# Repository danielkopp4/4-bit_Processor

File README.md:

# 4-bit_Processor
This is a project to build a fully working 4-bit processor made with discrete logic gates.
The processor is programmed with an Arduino MEGA and can be programmed in the assembly language based off of my architecture.

The schematics can currently be found in the Schematics branch. The file type of the schematics is for KiCAD.
The RAM and ROM have an associated PCB design.

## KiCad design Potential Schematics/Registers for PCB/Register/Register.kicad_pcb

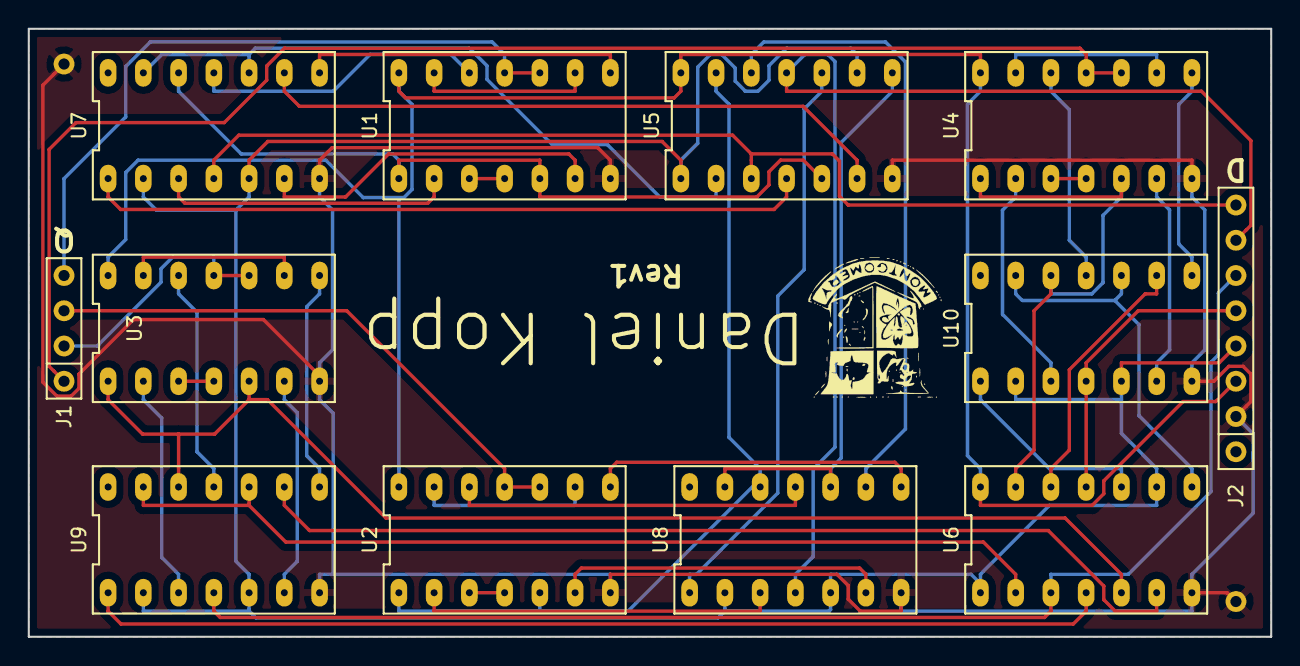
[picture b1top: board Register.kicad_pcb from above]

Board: 2 copper layers, 89.5 x 43.8 mm, 15 parts (0 on the bottom side), 51 nets.

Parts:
 : Measurement_Point_Round-TH_Small
 #2: Measurement_Point_Round-TH_Small
 #3: Real_Logo
J1: Conn_01x04_Female; Female_Header_4-pin
J2: Conn_01x08_Female; Female_Header_8-pin
U1, U2, U3, U4: 74LS02; DIP-14_300_ELL
U5, U6: 74LS04; DIP-14_300_ELL
U7, U8, U9, U10: 74LS08; DIP-14_300_ELL

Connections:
/D_Flip-Flop/D_Latch/QN: U1.3, U1.4
/D_Flip-Flop/D_Latch/RS-Latch/R: U1.2, U7.3
/D_Flip-Flop/D_Latch/RS-Latch/S: U1.6, U7.6
/D_Flip-Flop/QN: U1.9, U1.13
/D_Flip-Flop/sheet5BAD013C/C: U5.2, U7.10, U7.13
/D_Flip-Flop/sheet5BAD013C/D: U1.1, U1.5, U5.5, U7.12
/D_Flip-Flop/sheet5BAD013C/RS-Latch/R: U1.8, U7.8
/D_Flip-Flop/sheet5BAD013C/RS-Latch/S: U1.12, U7.11
/sheet5BAD03B0/D_Latch/QN: U2.3, U2.4
/sheet5BAD03B0/D_Latch/RS-Latch/R: U2.2, U8.3
/sheet5BAD03B0/D_Latch/RS-Latch/S: U2.6, U8.6
/sheet5BAD03B0/QN: U2.9, U2.13
/sheet5BAD03B0/sheet5BAD013C/C: U5.8, U8.10, U8.13
/sheet5BAD03B0/sheet5BAD013C/D: U2.1, U2.5, U5.13, U8.12
/sheet5BAD03B0/sheet5BAD013C/RS-Latch/R: U2.8, U8.8
/sheet5BAD03B0/sheet5BAD013C/RS-Latch/S: U2.12, U8.11
/sheet5BAD03B9/D_Latch/QN: U3.3, U3.4
/sheet5BAD03B9/D_Latch/RS-Latch/R: U3.2, U9.3
/sheet5BAD03B9/D_Latch/RS-Latch/S: U3.6, U9.6
/sheet5BAD03B9/QN: U3.9, U3.13
/sheet5BAD03B9/sheet5BAD013C/C: U6.2, U9.10, U9.13
/sheet5BAD03B9/sheet5BAD013C/D: U3.1, U3.5, U6.5, U9.12
/sheet5BAD03B9/sheet5BAD013C/RS-Latch/R: U3.8, U9.8
/sheet5BAD03B9/sheet5BAD013C/RS-Latch/S: U3.12, U9.11
/sheet5BAD03C0/D_Latch/QN: U4.3, U4.4
/sheet5BAD03C0/D_Latch/RS-Latch/R: U4.2, U10.3
/sheet5BAD03C0/D_Latch/RS-Latch/S: U4.6, U10.6
/sheet5BAD03C0/QN: U4.9, U4.13
/sheet5BAD03C0/sheet5BAD013C/C: U6.8, U10.10, U10.13
/sheet5BAD03C0/sheet5BAD013C/D: U4.1, U4.5, U6.13, U10.12
/sheet5BAD03C0/sheet5BAD013C/RS-Latch/R: U4.8, U10.8
/sheet5BAD03C0/sheet5BAD013C/RS-Latch/S: U4.12, U10.11
Clock: J2.4, U5.1, U5.9, U6.1, U6.9, U7.2, U7.5, U8.2, U8.5, U9.2, U9.5, U10.2, U10.5
D0: J2.8, U5.3, U7.4
D1: J2.7, U5.11, U8.4
D2: J2.6, U6.3, U9.4
D3: J2.5, U6.11, U10.4
GND: .1, #2.1, J2.2, U1.7, U2.7, U3.7, U4.7, U5.7, U6.7, U7.7, U8.7, U9.7, U10.7
unnamed: U5.4, U7.1
unnamed: U5.6, U7.9
unnamed: U5.10, U8.1
unnamed: U5.12, U8.9
unnamed: U6.4, U9.1
unnamed: U6.6, U9.9
unnamed: U6.10, U10.1
unnamed: U6.12, U10.9
Q0: J1.4, U1.10, U1.11
Q1: J1.3, U2.10, U2.11
Q2: J1.2, U3.10, U3.11
Q3: J1.1, U4.10, U4.11
VCC: J2.3, U1.14, U2.14, U3.14, U4.14, U5.14, U6.14

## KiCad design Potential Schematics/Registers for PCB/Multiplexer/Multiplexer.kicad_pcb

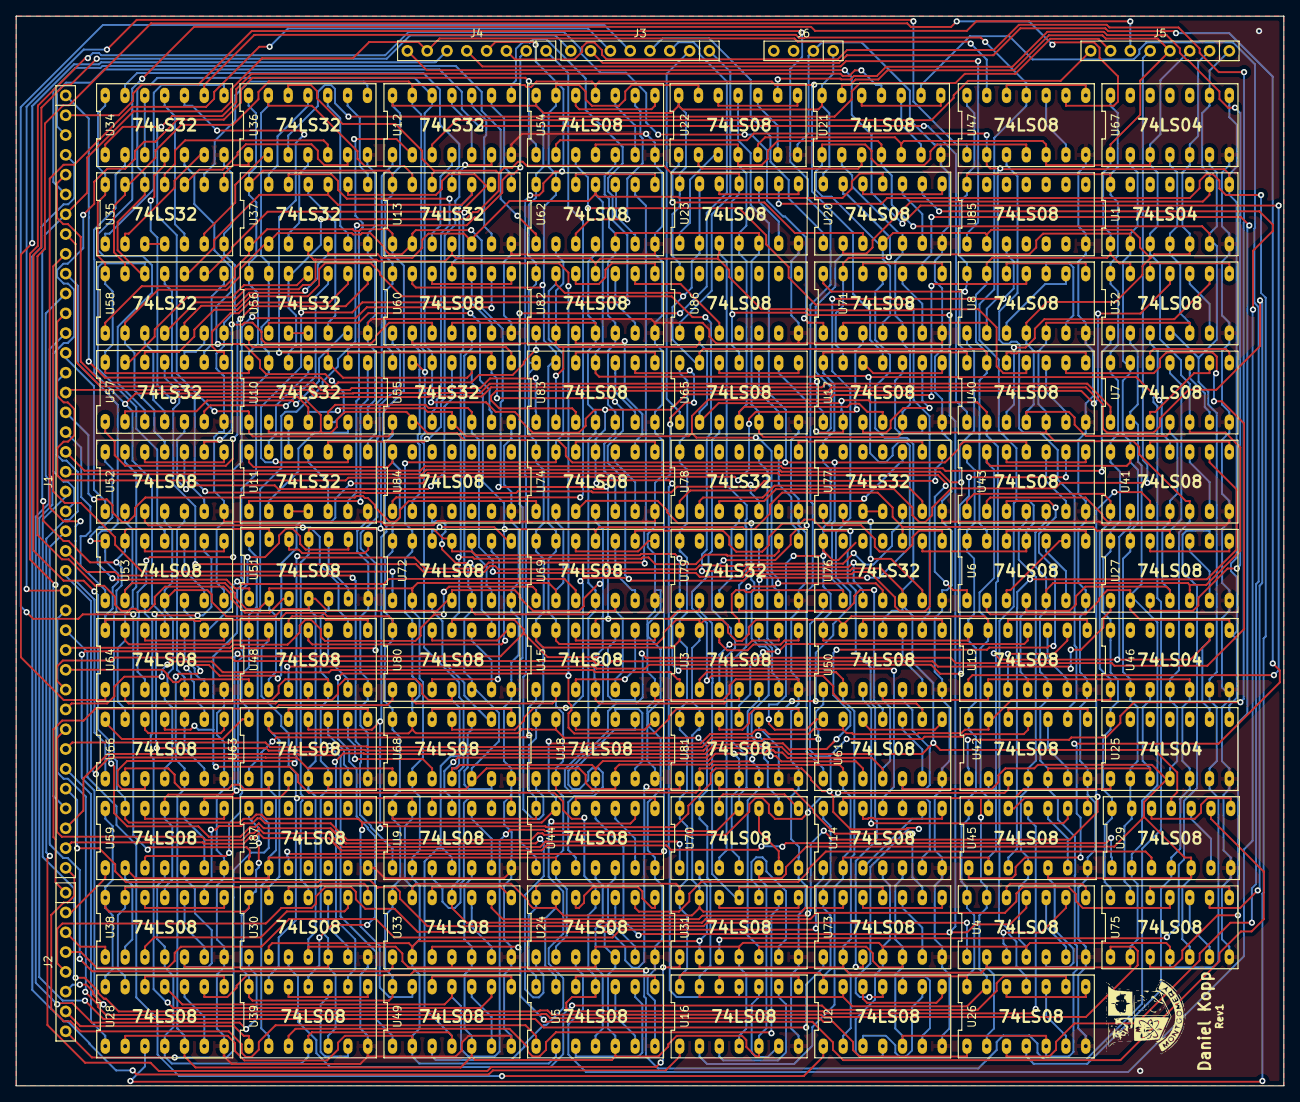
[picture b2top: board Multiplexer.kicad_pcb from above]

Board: 2 copper layers, 162.6 x 137.2 mm, 93 parts (0 on the bottom side), 341 nets.

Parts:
J1: Conn_01x40_Female; SIP-40
J2, J3, J4, J5: Conn_01x08_Female; Female_Header_8-pin
J6: Conn_01x04_Female; Female_Header_4-pin
U1, U25, U46, U67: 74LS04; DIP-14_300_ELL
U2, U3, U4, U5, U6, U7, U8, U9, U14, U15, U16, U17, U18, U19, U20, U21, U22, U23, U24, U26, U27, U28, U29, U30, U31, U32, U33, U38, U39, U40, U41, U42, U43, U44, U45, U47, U48, U49, U50, U51, U52, U53, U54, U59, U60, U61, U62, U63, U64, U65, U66, U68, U69, U70, U71, U72, U73, U74, U75, U80, U81, U82, U83, U84, U85, U86, U87: 74LS08; DIP-14_300_ELL
U10, U11, U12, U13, U34, U35, U36, U37, U55, U56, U57, U58, U76, U77, U78, U79: 74LS32; DIP-14_300_ELL

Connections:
/64:4 Multiplexer/16;1_Multiplexer/5:1_AND/b: U1.8, U2.2, U3.2, U4.2, U5.2, U6.2, U7.2, U8.2, U9.2, U25.8, U26.2, U27.2, U28.2, U29.2, U30.2, U31.2, U32.2, U33.2, U46.8, U47.2, U48.2, U49.2, U50.2, U51.2, U52.2, U53.2, U54.2, U67.8, U68.2, U69.2, U70.2, U71.2, U72.2, U73.2, U74.2, U75.2
/64:4 Multiplexer/16;1_Multiplexer/5:1_AND/c: U1.6, U2.4, U3.4, U4.4, U5.4, U14.4, U15.4, U16.4, U17.4, U21.4, U22.4, U23.4, U24.4, U25.6, U30.4, U31.4, U32.4, U33.4, U42.4, U43.4, U44.4, U45.4, U46.6, U51.4, U52.4, U53.4, U54.4, U63.4, U64.4, U65.4, U66.4, U67.6, U72.4, U73.4, U74.4, U75.4
/64:4 Multiplexer/16;1_Multiplexer/5:1_AND/d: U1.4, U4.5, U5.5, U8.5, U9.5, U16.5, U17.5, U20.5, U21.2, U23.5, U24.5, U25.4, U28.5, U29.5, U32.5, U33.5, U40.5, U41.5, U44.5, U45.5, U46.4, U49.5, U50.5, U53.5, U54.5, U61.5, U62.5, U65.5, U66.5, U67.4, U70.5, U71.5, U74.5, U75.5, U82.5, U83.5
/64:4 Multiplexer/16;1_Multiplexer/5:1_AND/e: U1.2, U3.13, U5.13, U7.13, U9.13, U15.13, U17.13, U19.13, U20.13, U22.13, U24.13, U25.2, U27.13, U29.13, U31.13, U33.13, U39.13, U41.13, U43.13, U45.13, U46.2, U48.13, U50.13, U52.13, U54.13, U60.13, U62.13, U64.13, U66.13, U67.2, U69.13, U71.13, U73.13, U75.13, U81.13, U83.13
/64:4 Multiplexer/16;1_Multiplexer/Sheet5BB0E1EE/D0: U5.11, U10.13, U13.13, U24.11, U36.13, U45.11, U56.13, U66.11
/64:4 Multiplexer/16;1_Multiplexer/Sheet5BB0E1EE/D1: U4.11, U10.12, U13.12, U23.11, U36.12, U44.11, U56.12, U65.11
/64:4 Multiplexer/16;1_Multiplexer/Sheet5BB0E1EE/D2: U3.11, U10.2, U22.11, U34.2, U43.11, U55.2, U64.11, U76.2
/64:4 Multiplexer/16;1_Multiplexer/Sheet5BB0E1EE/D3: U2.11, U10.1, U21.11, U34.1, U42.11, U55.1, U63.11, U76.1
/64:4 Multiplexer/16;1_Multiplexer/Sheet5BB0E1EE/D4: U9.11, U10.5, U29.11, U34.5, U50.11, U55.5, U71.11, U76.5
/64:4 Multiplexer/16;1_Multiplexer/Sheet5BB0E1EE/D5: U8.11, U10.4, U28.11, U34.4, U49.11, U55.4, U70.11, U76.4
/64:4 Multiplexer/16;1_Multiplexer/Sheet5BB0E1EE/D6: U7.11, U10.10, U27.11, U34.10, U48.11, U55.10, U69.11, U76.10
/64:4 Multiplexer/16;1_Multiplexer/Sheet5BB0E1EE/D7: U6.11, U10.9, U26.11, U34.9, U47.11, U55.9, U68.11, U76.9
/64:4 Multiplexer/16;1_Multiplexer/Sheet5BB0E1EE/D8: U12.13, U17.11, U33.11, U35.13, U54.11, U55.13, U58.13, U75.11
/64:4 Multiplexer/16;1_Multiplexer/Sheet5BB0E1EE/D9: U12.12, U16.11, U32.11, U35.12, U53.11, U55.12, U58.12, U74.11
/64:4 Multiplexer/16;1_Multiplexer/Sheet5BB0E1EE/Da: U13.2, U15.11, U31.11, U37.2, U52.11, U58.2, U73.11, U79.2
/64:4 Multiplexer/16;1_Multiplexer/Sheet5BB0E1EE/Db: U13.1, U14.11, U30.11, U37.1, U51.11, U58.1, U72.11, U79.1
/64:4 Multiplexer/16;1_Multiplexer/Sheet5BB0E1EE/Dc: U13.5, U20.11, U37.5, U41.11, U58.5, U62.11, U79.5, U83.11
/64:4 Multiplexer/16;1_Multiplexer/Sheet5BB0E1EE/Dd: U13.4, U23.3, U37.4, U40.11, U58.4, U61.11, U79.4, U82.11
/64:4 Multiplexer/16;1_Multiplexer/Sheet5BB0E1EE/De: U13.10, U19.11, U37.10, U39.11, U58.10, U60.11, U79.10, U81.11
/64:4 Multiplexer/16;1_Multiplexer/Sheet5BB0E1EE/Df: U13.9, U18.11, U37.9, U38.11, U58.9, U59.11, U79.9, U80.11
/64:4 Multiplexer/D00: J1.40, U5.1
/64:4 Multiplexer/D01: J1.39, U29.1
/64:4 Multiplexer/D02: J1.38, U50.1
/64:4 Multiplexer/D03: J1.37, U71.1
/64:4 Multiplexer/D10: J1.36, U4.1
/64:4 Multiplexer/D11: J1.35, U28.1
/64:4 Multiplexer/D12: J1.34, U49.1
/64:4 Multiplexer/D13: J1.33, U70.1
/64:4 Multiplexer/D20: J1.32, U3.1
/64:4 Multiplexer/D21: J1.31, U27.1
/64:4 Multiplexer/D22: J1.30, U48.1
/64:4 Multiplexer/D23: J1.29, U69.1
/64:4 Multiplexer/D30: J1.28, U2.1
/64:4 Multiplexer/D31: J1.27, U26.1
/64:4 Multiplexer/D32: J1.26, U47.1
/64:4 Multiplexer/D33: J1.25, U68.1
/64:4 Multiplexer/D40: J1.24, U9.1
/64:4 Multiplexer/D41: J1.23, U33.1
/64:4 Multiplexer/D42: J1.22, U54.1
/64:4 Multiplexer/D43: J1.21, U75.1
/64:4 Multiplexer/D50: J1.20, U8.1
/64:4 Multiplexer/D51: J1.19, U32.1
/64:4 Multiplexer/D52: J1.18, U53.1
/64:4 Multiplexer/D53: J1.17, U74.1
/64:4 Multiplexer/D60: J1.16, U7.1
/64:4 Multiplexer/D61: J1.15, U31.1
/64:4 Multiplexer/D62: J1.14, U52.1
/64:4 Multiplexer/D63: J1.13, U73.1
/64:4 Multiplexer/D70: J1.12, U6.1
/64:4 Multiplexer/D71: J1.11, U30.1
/64:4 Multiplexer/D72: J1.10, U51.1
/64:4 Multiplexer/D73: J1.9, U72.1
/64:4 Multiplexer/D80: J1.8, U17.1
/64:4 Multiplexer/D81: J1.7, J4.7, U41.1, U42.13, U43.1, U44.13, U46.1, U47.13, U49.13, U51.13, U53.13, U59.13, U61.13
/64:4 Multiplexer/D82: J1.6, U62.1
/64:4 Multiplexer/D83: J1.5, U83.1
/64:4 Multiplexer/D90: J1.4, U16.1
/64:4 Multiplexer/D91: J1.3, U40.1
/64:4 Multiplexer/D92: J1.2, U61.1
/64:4 Multiplexer/D93: J1.1, U82.1
/64:4 Multiplexer/Da0: J2.8, U15.1
/64:4 Multiplexer/Da1: J2.7, U39.1
/64:4 Multiplexer/Da2: J2.6, U60.1
/64:4 Multiplexer/Da3: J2.5, U81.1
/64:4 Multiplexer/Db0: J2.4, U14.1
/64:4 Multiplexer/Db1: J2.3, U38.1
/64:4 Multiplexer/Db2: J2.2, U59.1
/64:4 Multiplexer/Db3: J2.1, U80.1
/64:4 Multiplexer/Dc0: J3.8, U24.1
/64:4 Multiplexer/Dc1: J3.7, U45.1
/64:4 Multiplexer/Dc2: J3.6, U66.1
/64:4 Multiplexer/Dc3: J3.5, U87.1
/64:4 Multiplexer/Dd0: J3.4, U20.1
/64:4 Multiplexer/Dd1: J3.3, U44.1
/64:4 Multiplexer/Dd2: J3.2, U65.1
/64:4 Multiplexer/Dd3: J3.1, U86.1
/64:4 Multiplexer/De0: J4.8, U19.1
/64:4 Multiplexer/De2: J4.6, U64.1
/64:4 Multiplexer/De3: J4.5, U85.1
/64:4 Multiplexer/Df0: J4.4, U18.1
/64:4 Multiplexer/Df1: J4.3, U42.1
/64:4 Multiplexer/Df2: J4.2, U63.1
/64:4 Multiplexer/Df3: J4.1, U84.1
/64:4 Multiplexer/Q0: J5.8, U12.3
/64:4 Multiplexer/Q1: J5.7, U36.3
/64:4 Multiplexer/Q2: J5.6, U57.3
/64:4 Multiplexer/Q3: J5.5, U78.3
/64:4 Multiplexer/S0: J5.4, U1.1, U2.13, U4.13, U6.13, U8.13, U14.13, U16.13, U18.13, U21.13, U23.2, U23.13, U25.1, U26.13, U28.13, U30.13, U32.13, U38.13, U40.13, U63.13, U65.13, U67.1, U68.13, U70.13, U72.13, U74.13, U80.13, U82.13
/64:4 Multiplexer/S1: J5.3, U1.3, U2.5, U3.5, U6.5, U7.5, U14.5, U15.5, U18.5, U19.5, U21.5, U22.5, U25.3, U26.5, U27.5, U30.5, U31.5, U38.5, U39.5, U42.5, U43.5, U46.3, U47.5, U48.5, U51.5, U52.5, U59.5, U60.5, U63.5, U64.5, U67.3, U68.5, U69.5, U72.5, U73.5, U80.5, U81.5
/64:4 Multiplexer/S2: J5.2, U1.5, U6.4, U7.4, U8.4, U9.4, U18.4, U19.2, U19.4, U20.4, U21.1, U25.5, U26.4, U27.4, U28.4, U29.4, U38.4, U39.4, U40.4, U41.4, U43.2, U46.5, U47.4, U48.4, U49.4, U50.4, U59.4, U60.4, U61.4, U62.4, U64.2, U67.5, U68.4, U69.4, U70.4, U71.4, U80.4, U81.4, U82.4, U83.4, U85.2
/64:4 Multiplexer/S3: J5.1, U1.9, U14.2, U15.2, U16.2, U17.2, U18.2, U20.2, U24.2, U25.9, U38.2, U39.2, U40.2, U41.2, U42.2, U44.2, U45.2, U46.9, U59.2, U60.2, U61.2, U62.2, U63.2, U65.2, U66.2, U67.9, U80.2, U81.2, U82.2, U83.2, U84.2, U86.2, U87.2
GND: J6.2, U1.7, U2.7, U3.7, U4.7, U5.7, U6.7, U7.7, U8.7, U9.7, U10.7, U11.7, U12.7, U13.7, U14.7, U15.7, U16.7, U17.7, U18.7, U19.7, U20.7, U21.7, U22.7, U23.7, U24.7, U25.7, U26.7, U27.7, U28.7, U29.7, U30.7, U31.7, U32.7, U33.7, U34.7, U35.7, U36.7, U37.7, U38.7, U39.7, U40.7, U41.7, U42.7, U43.7, U44.7, U45.7, U46.7, U47.7, U48.7, U49.7, U50.7, U51.7, U52.7, U53.7, U54.7, U55.7, U56.7, U57.7, U58.7, U59.7, U60.7, U61.7, U62.7, U63.7, U64.7, U65.7, U66.7, U67.7, U68.7, U69.7, U70.7, U71.7, U72.7, U73.7, U74.7, U75.7, U76.7, U77.7, U78.7, U79.7, U80.7, U81.7, U82.7, U83.7, U84.7, U85.7, U86.7, U87.7
unnamed: U2.3, U2.9
unnamed: U2.6, U2.10
unnamed: U2.8, U2.12
unnamed: U3.3, U3.9
unnamed: U3.6, U3.10
unnamed: U3.8, U3.12
unnamed: U4.3, U4.9
unnamed: U4.6, U4.10
unnamed: U4.8, U4.12
unnamed: U5.3, U5.9
unnamed: U5.6, U5.10
unnamed: U5.8, U5.12
unnamed: U6.3, U6.9
unnamed: U6.6, U6.10
unnamed: U6.8, U6.12
unnamed: U7.3, U7.9
unnamed: U7.6, U7.10
unnamed: U7.8, U7.12
unnamed: U8.3, U8.9
unnamed: U8.6, U8.10
unnamed: U8.8, U8.12
unnamed: U9.3, U9.9
unnamed: U9.6, U9.10
unnamed: U9.8, U9.12
unnamed: U10.3, U11.12
unnamed: U10.6, U11.2
unnamed: U10.8, U11.1
unnamed: U10.11, U11.13
unnamed: U11.3, U11.4
unnamed: U11.6, U12.2
unnamed: U11.8, U12.1
unnamed: U11.9, U12.8
unnamed: U11.10, U12.6
unnamed: U11.5, U11.11
unnamed: U12.4, U13.3
unnamed: U12.9, U13.8
unnamed: U12.10, U13.6
unnamed: U12.5, U12.11
unnamed: U13.11, U34.13
unnamed: U14.3, U14.9
unnamed: U14.6, U14.10
unnamed: U14.8, U14.12
unnamed: U15.3, U15.9
unnamed: U15.6, U15.10
unnamed: U15.8, U15.12
unnamed: U16.3, U16.9
unnamed: U16.6, U16.10
unnamed: U16.8, U16.12
unnamed: U17.3, U17.9
unnamed: U17.6, U17.10
unnamed: U17.8, U17.12
unnamed: U18.3, U18.9
unnamed: U18.6, U18.10
unnamed: U18.8, U18.12
unnamed: U19.3, U19.9
unnamed: U19.6, U19.10
unnamed: U19.8, U19.12
unnamed: U20.3, U22.1
unnamed: U20.9, U24.3
unnamed: U20.6, U20.10
unnamed: U20.8, U20.12
unnamed: U21.3, U22.2
unnamed: U21.9, U26.3
unnamed: U21.6, U21.10
unnamed: U21.8, U21.12
unnamed: U22.3, U23.1
unnamed: U22.9, U27.3
unnamed: U22.6, U22.10
unnamed: U22.8, U22.12
unnamed: U23.9, U28.3
unnamed: U23.6, U23.10
unnamed: U23.8, U23.12
unnamed: U24.9, U29.3
unnamed: U24.6, U24.10
unnamed: U24.8, U24.12
unnamed: U26.9, U30.3
unnamed: U26.6, U26.10
unnamed: U26.8, U26.12
unnamed: U27.9, U31.3
unnamed: U27.6, U27.10
unnamed: U27.8, U27.12
unnamed: U28.9, U32.3
unnamed: U28.6, U28.10
unnamed: U28.8, U28.12
unnamed: U29.9, U33.3
unnamed: U29.6, U29.10
unnamed: U29.8, U29.12
unnamed: U30.9, U38.3
unnamed: U30.6, U30.10
unnamed: U30.8, U30.12
unnamed: U31.9, U39.3
unnamed: U31.6, U31.10
unnamed: U31.8, U31.12
unnamed: U32.9, U40.3
unnamed: U32.6, U32.10
unnamed: U32.8, U32.12
unnamed: U33.9, U41.3
unnamed: U33.6, U33.10
unnamed: U33.8, U33.12
unnamed: U34.6, U35.2
unnamed: U34.8, U35.1
unnamed: U34.11, U35.5
unnamed: U34.3, U34.12
unnamed: U35.3, U35.4
unnamed: U35.6, U36.2
unnamed: U35.8, U36.1
unnamed: U35.9, U36.8
unnamed: U35.10, U36.6
unnamed: U35.11, U36.5
unnamed: U36.4, U37.3
unnamed: U36.9, U37.8
unnamed: U36.10, U37.6
unnamed: U36.11, U37.13
unnamed: U37.11, U56.5
unnamed: U37.12, U55.3
unnamed: U38.9, U42.3
unnamed: U38.6, U38.10
unnamed: U38.8, U38.12
unnamed: U39.9, U43.3
unnamed: U39.6, U39.10
unnamed: U39.8, U39.12
unnamed: U40.9, U44.3
unnamed: U40.6, U40.10
unnamed: U40.8, U40.12
unnamed: U41.9, U45.3
unnamed: U41.6, U41.10
unnamed: U41.8, U41.12
unnamed: U42.9, U47.3
unnamed: U42.6, U42.10
unnamed: U42.8, U42.12
unnamed: U43.9, U48.3
unnamed: U43.6, U43.10
unnamed: U43.8, U43.12
unnamed: U44.9, U49.3
unnamed: U44.6, U44.10
unnamed: U44.8, U44.12
unnamed: U45.9, U50.3
unnamed: U45.6, U45.10
unnamed: U45.8, U45.12
unnamed: U47.9, U51.3
unnamed: U47.6, U47.10
unnamed: U47.8, U47.12
unnamed: U48.9, U52.3
unnamed: U48.6, U48.10
unnamed: U48.8, U48.12
unnamed: U49.9, U53.3
unnamed: U49.6, U49.10
unnamed: U49.8, U49.12
unnamed: U50.9, U54.3
unnamed: U50.6, U50.10
unnamed: U50.8, U50.12
unnamed: U51.9, U59.3
unnamed: U51.6, U51.10
unnamed: U51.8, U51.12
unnamed: U52.9, U60.3
unnamed: U52.6, U52.10
unnamed: U52.8, U52.12
unnamed: U53.9, U61.3
unnamed: U53.6, U53.10
unnamed: U53.8, U53.12
unnamed: U54.9, U62.3
unnamed: U54.6, U54.10
unnamed: U54.8, U54.12
unnamed: U55.6, U56.2
unnamed: U55.8, U56.1
unnamed: U55.11, U57.5
unnamed: U56.3, U56.4
unnamed: U56.6, U57.2
unnamed: U56.8, U57.1
unnamed: U56.9, U57.8
unnamed: U56.10, U57.6
unnamed: U56.11, U57.13
unnamed: U57.4, U58.3
unnamed: U57.9, U58.8
unnamed: U57.10, U58.6
unnamed: U57.11, U77.5
unnamed: U57.12, U76.3
unnamed: U58.11, U78.5
unnamed: U59.9, U63.3
unnamed: U59.6, U59.10
unnamed: U59.8, U59.12
unnamed: U60.9, U64.3
unnamed: U60.6, U60.10
unnamed: U60.8, U60.12
unnamed: U61.9, U65.3
unnamed: U61.6, U61.10
unnamed: U61.8, U61.12
unnamed: U62.9, U66.3
unnamed: U62.6, U62.10
unnamed: U62.8, U62.12
unnamed: U63.9, U68.3
unnamed: U63.6, U63.10
unnamed: U63.8, U63.12
unnamed: U64.9, U69.3
unnamed: U64.6, U64.10
unnamed: U64.8, U64.12
unnamed: U65.9, U70.3
unnamed: U65.6, U65.10
unnamed: U65.8, U65.12
unnamed: U66.9, U71.3
unnamed: U66.6, U66.10
unnamed: U66.8, U66.12
unnamed: U68.9, U72.3
unnamed: U68.6, U68.10
unnamed: U68.8, U68.12
unnamed: U69.9, U73.3
unnamed: U69.6, U69.10
unnamed: U69.8, U69.12
unnamed: U70.9, U74.3
unnamed: U70.6, U70.10
unnamed: U70.8, U70.12
unnamed: U71.9, U75.3
unnamed: U71.6, U71.10
unnamed: U71.8, U71.12
unnamed: U72.9, U80.3
unnamed: U72.6, U72.10
unnamed: U72.8, U72.12
unnamed: U73.9, U81.3
unnamed: U73.6, U73.10
unnamed: U73.8, U73.12
unnamed: U74.9, U82.3
unnamed: U74.6, U74.10
unnamed: U74.8, U74.12
unnamed: U75.9, U83.3
unnamed: U75.6, U75.10
unnamed: U75.8, U75.12
unnamed: U76.6, U77.2
unnamed: U76.8, U77.1
unnamed: U77.3, U77.4
unnamed: U77.6, U78.2
unnamed: U77.8, U78.1
unnamed: U77.9, U78.8
unnamed: U77.10, U78.6
unnamed: U78.4, U79.3
unnamed: U78.9, U79.8
unnamed: U78.10, U79.6
unnamed: U80.9, U84.3
unnamed: U80.6, U80.10
unnamed: U80.8, U80.12
unnamed: U81.9, U85.3
unnamed: U81.6, U81.10
unnamed: U81.8, U81.12
unnamed: U82.9, U86.3
unnamed: U82.6, U82.10
unnamed: U82.8, U82.12
unnamed: U83.9, U87.3
unnamed: U83.6, U83.10
unnamed: U83.8, U83.12
VCC: J6.1, U1.14, U2.14, U3.14, U4.14, U5.14, U6.14, U7.14, U8.14, U9.14, U10.14, U11.14, U12.14, U13.14, U14.14, U15.14, U16.14, U17.14, U18.14, U19.14, U20.14, U21.14, U22.14, U23.14, U24.14, U25.14, U26.14, U27.14, U28.14, U29.14, U30.14, U31.14, U32.14, U33.14, U34.14, U35.14, U36.14, U37.14, U38.14, U39.14, U40.14, U41.14, U42.14, U43.14, U44.14, U45.14, U46.14, U47.14, U48.14, U49.14, U50.14, U51.14, U52.14, U53.14, U54.14, U55.14, U56.14, U57.14, U58.14, U59.14, U60.14, U61.14, U62.14, U63.14, U64.14, U65.14, U66.14, U67.14, U68.14, U69.14, U70.14, U71.14, U72.14, U73.14, U74.14, U75.14, U76.14, U77.14, U78.14, U79.14, U80.14, U81.14, U82.14, U83.14, U84.14, U85.14, U86.14, U87.14

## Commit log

2018-09-09 Added assembly code parser v0.01 Beta untested
2018-09-09 Added basic description to README.md
2018-09-10 Creates frame work for instruction to hex compiler
2018-09-10 Added english parser
2018-09-11 Made Half_ALU and Framework
2018-09-11 Made an unknown update
2018-09-14 Made Full ALU
2018-09-15 Made the registers
2018-09-16 Added Registers to Top Schematic
2018-09-18 Minor Changes
2018-09-18 Adding Multiply Devide
2018-09-20 Finished PCB
2018-09-23 Finished PCB designes for Multiplexer and Registers
2018-09-23 Updated parser with assembly code instructions
2018-09-24 Updated PCB and is ready to be ordered
2018-09-25 Working on Multiplier
2018-09-25 The last commit wasnt pushed so it is being merged
2018-09-26 Made Multiplier
2018-09-27 Updated overview of Schematic
2018-10-03 In the middle of adding ROM
